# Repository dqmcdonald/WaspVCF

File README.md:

# WaspVCF
 EDP Wasp Voltage Controlled Filter

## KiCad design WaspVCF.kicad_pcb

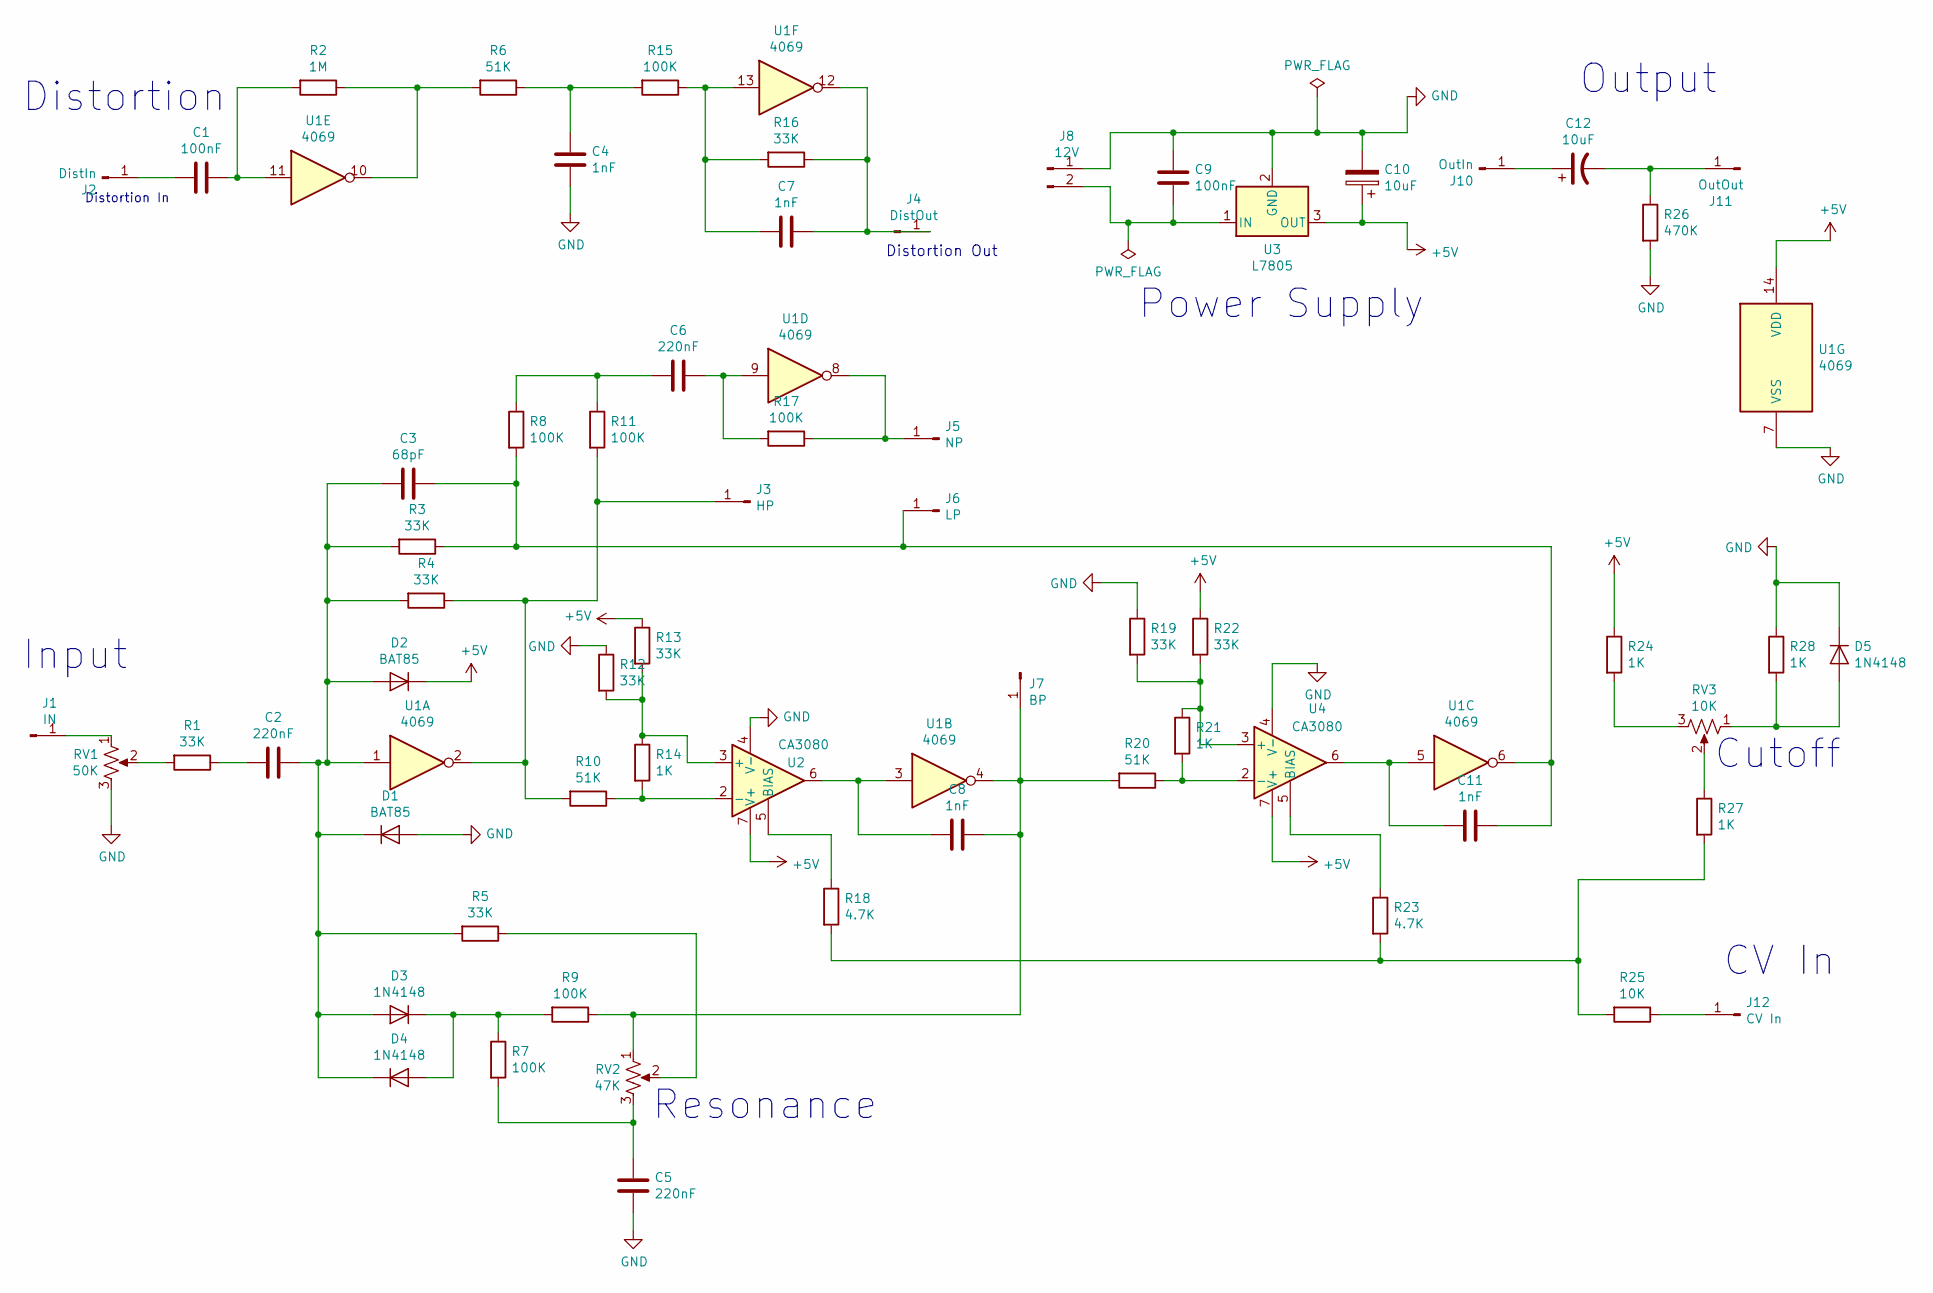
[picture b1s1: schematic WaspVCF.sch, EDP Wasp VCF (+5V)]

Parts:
C1, C9: 100nF; C_Disc_D6.0mm_W2.5mm_P5.00mm
C2, C5, C6: 220nF; C_Disc_D6.0mm_W2.5mm_P5.00mm
C3: 68pF; C_Disc_D6.0mm_W2.5mm_P5.00mm
C4, C7, C8, C11: 1nF; C_Disc_D6.0mm_W2.5mm_P5.00mm
C10, C12: 10uF; CP_Radial_D5.0mm_P2.50mm
D1, D2: BAT85; D_T-1_P5.08mm_Horizontal
D3, D4, D5: 1N4148; D_T-1_P5.08mm_Horizontal
J1: IN; Pin_Header_Straight_1x01_Pitch2.54mm
J2: DistIn; Pin_Header_Straight_1x01_Pitch2.54mm
J3: HP; Pin_Header_Straight_1x01_Pitch2.54mm
J4: DistOut; Pin_Header_Straight_1x01_Pitch2.54mm
J5: NP; Pin_Header_Straight_1x01_Pitch2.54mm
J6: LP; Pin_Header_Straight_1x01_Pitch2.54mm
J7: BP; Pin_Header_Straight_1x01_Pitch2.54mm
J8: 12V; Pin_Header_Straight_1x02_Pitch2.54mm
J10: OutIn; Pin_Header_Straight_1x01_Pitch2.54mm
J11: OutOut; Pin_Header_Straight_1x01_Pitch2.54mm
J12: CV In; Pin_Header_Straight_1x01_Pitch2.54mm
R1, R3, R4, R5, R12, R13, R16, R19, R22: 33K; R_Axial_DIN0207_L6.3mm_D2.5mm_P7.62mm_Horizontal
R2: 1M; R_Axial_DIN0207_L6.3mm_D2.5mm_P7.62mm_Horizontal
R6, R10, R20: 51K; R_Axial_DIN0207_L6.3mm_D2.5mm_P7.62mm_Horizontal
R7, R8, R9, R11, R15, R17: 100K; R_Axial_DIN0207_L6.3mm_D2.5mm_P7.62mm_Horizontal
R14, R21, R24, R27, R28: 1K; R_Axial_DIN0207_L6.3mm_D2.5mm_P7.62mm_Horizontal
R18, R23: 4.7K; R_Axial_DIN0207_L6.3mm_D2.5mm_P7.62mm_Horizontal
R25: 10K; R_Axial_DIN0207_L6.3mm_D2.5mm_P7.62mm_Horizontal
R26: 470K; R_Axial_DIN0207_L6.3mm_D2.5mm_P7.62mm_Horizontal
RV1: 50K; Pin_Header_Straight_1x03_Pitch2.54mm
RV2: 47K; Pin_Header_Straight_1x03_Pitch2.54mm
RV3: 10K; Pin_Header_Straight_1x03_Pitch2.54mm
U1: 4069; DIP-14_W7.62mm_Socket_LongPads
U2: CA3080; DIP-8_W7.62mm_Socket_LongPads
U3: L7805; TO-220-3_Vertical
U4: CA3080; DIP-8_W7.62mm_LongPads

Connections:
+5V: C10.1, D2.1 (K), R13.1, R22.1, R24.1, U1.14 (VDD), U2.7 (V+), U3.3 (OUT), U4.7 (V+)
GND: C4.2, C5.2, C9.1, C10.2, D1.2 (A), D5.1 (K), J8.1, R12.1, R19.1, R26.2, R28.1, RV1.3, U1.7 (VSS), U2.4 (V-), U3.2 (GND), U4.4 (V-)
unnamed: C1.1, R2.2, U1.11
unnamed: C1.2, J2.1
unnamed: C2.1, C3.2, D1.1 (K), D2.2 (A), D3.2 (A), D4.1 (K), R3.2, R4.2, R5.2, U1.1
unnamed: C2.2, R1.1
unnamed: C4.1, R6.1, R15.2
unnamed: C5.1, R7.2, RV2.3
unnamed: C6.1, R17.2, U1.9
unnamed: C6.2, R8.1, R11.1
unnamed: C7.1, J4.1, R16.1, U1.12
unnamed: C7.2, R15.1, R16.2, U1.13
unnamed: C8.1, J7.1, R9.1, R20.2, RV2.1, U1.4
unnamed: C8.2, U1.3, U2.6
unnamed: C9.2, J8.2, U3.1 (IN)
unnamed: C3.1, C11.1, J6.1, R3.1, R8.2, U1.6
unnamed: C11.2, U1.5, U4.6
unnamed: C12.1, J10.1
unnamed: C12.2, J11.1, R26.1
unnamed: D3.1 (K), D4.2 (A), R7.1, R9.2
unnamed: D5.2 (A), R28.2, RV3.1
unnamed: J1.1, RV1.1
unnamed: J3.1, R4.1, R10.2, R11.2, U1.2
unnamed: J5.1, R17.1, U1.8
unnamed: J12.1, R25.1
unnamed: R1.2, RV1.2
unnamed: R2.1, R6.2, U1.10
unnamed: R5.1, RV2.2
unnamed: R10.1, R14.2, U2.2 (-)
unnamed: R12.2, R13.2, R14.1, U2.3 (+)
unnamed: R18.1, U2.5 (BIAS)
unnamed: R18.2, R23.2, R25.2, R27.2
unnamed: R19.2, R21.1, R22.2, U4.3 (+)
unnamed: R20.1, R21.2, U4.2 (-)
unnamed: R23.1, U4.5 (BIAS)
unnamed: R24.2, RV3.3
unnamed: R27.1, RV3.2

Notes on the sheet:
Distortion In
Distortion
Output
CV In
Resonance
Cutoff
Power Supply
Input
Distortion Out

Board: 2 copper layers, 63 parts (0 on the bottom side), 37 nets, no tracks yet.

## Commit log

2019-12-18 Added Distotion and Output to the Schematic
2019-12-22 Completed Schematic
    Annotations and ERC done
2019-12-22 Assigned Footprints
